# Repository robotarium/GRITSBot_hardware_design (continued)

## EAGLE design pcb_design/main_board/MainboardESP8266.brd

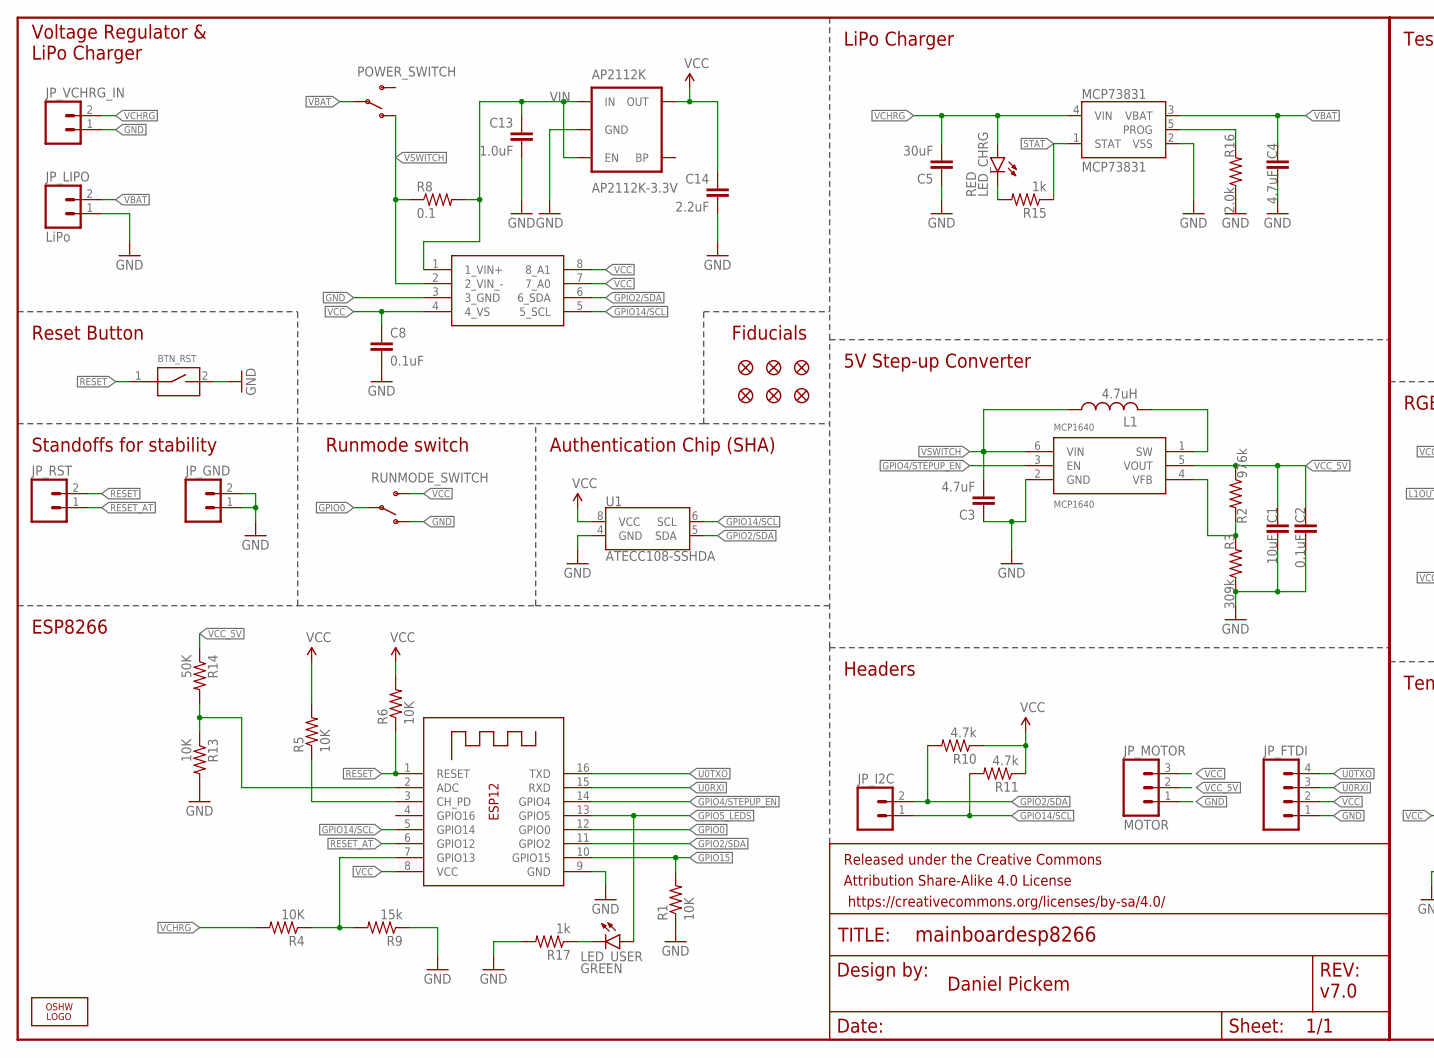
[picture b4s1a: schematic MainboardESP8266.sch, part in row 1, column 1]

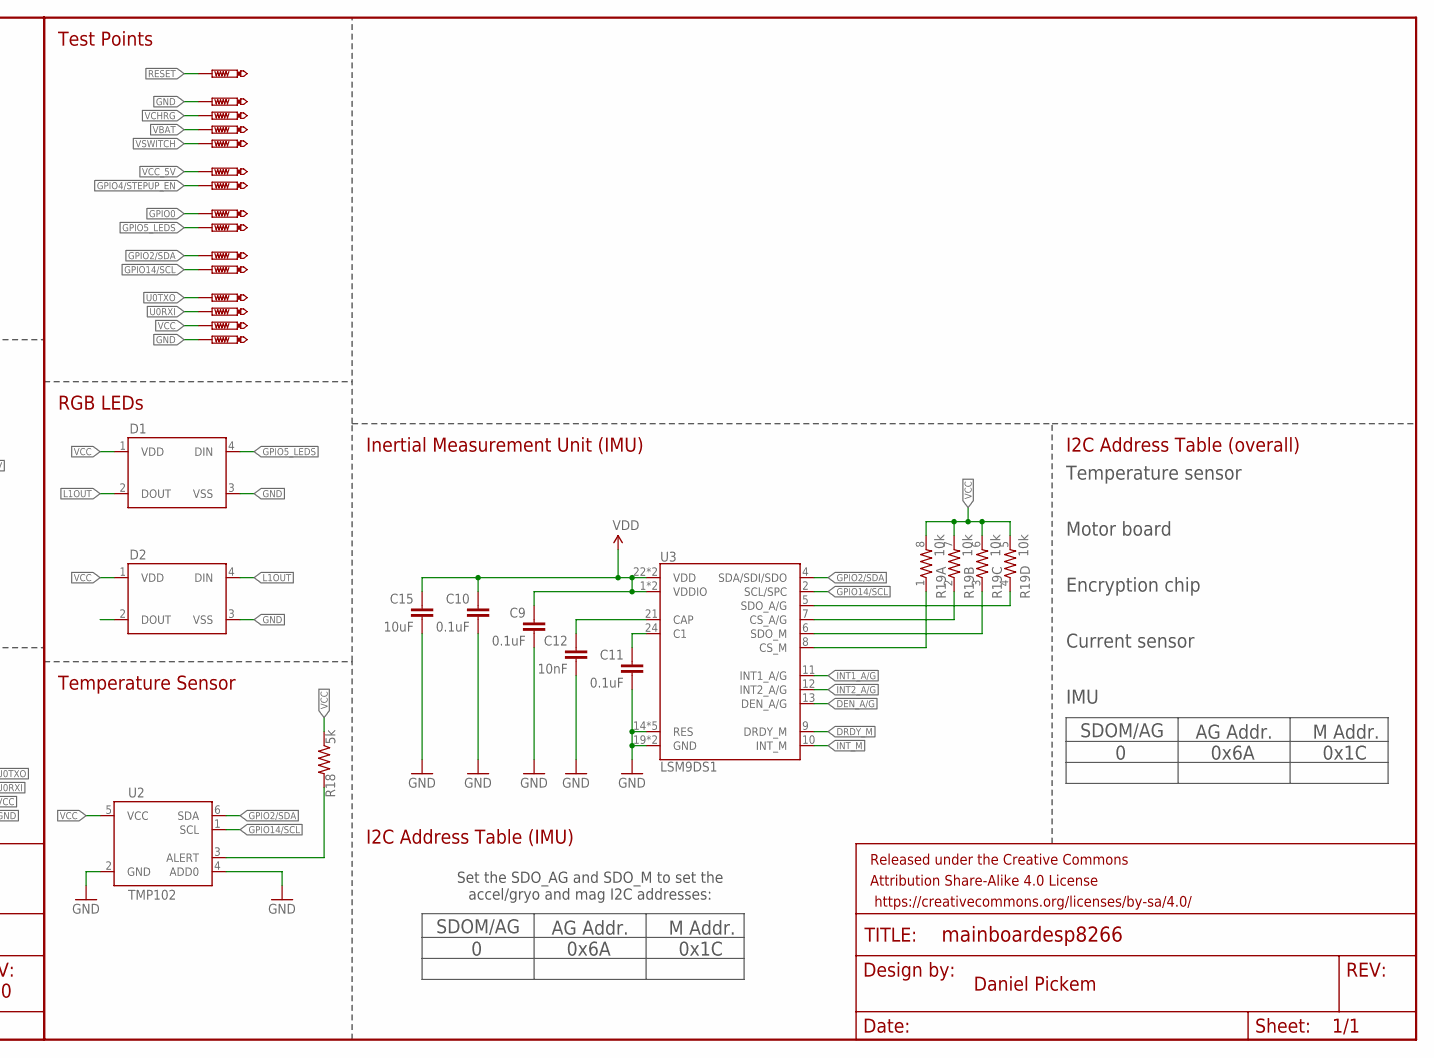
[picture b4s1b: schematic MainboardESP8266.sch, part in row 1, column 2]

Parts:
AP2112K: AP2112K-3.3V; SOT23-5
BTN_RST: BUTTON_TACTILE_SLIM
C1: 10uF; 0603-CAP@1
C2, C8: 0.1uF; 0603-CAP@1
C3, C4: 4.7uF; 0603-CAP@1
C5: 30uF; 1206
C9, C10, C11: 0.1uF; 0603-CAP
C12: 10nF; 0603-CAP
C13: 1.0uF; 0805
C14: 2.2uF; 0603-CAP@1
C15: 10uF; 0603-CAP
D1, D2: WS2812B
ESP8266: ESP-12; ESP-12-07
FRAME1, FRAME2: FRAME-LETTER; CREATIVE_COMMONS
INA219: INA219; SOT-23-8
JP1, JP2, JP3, JP4, JP5, JP6: FIDUCIAL1X2.5; FIDUCIAL-1X2.5
JP_FTDI: M041X04_NO_SILK; 1X04_NO_SILK
JP_GND: M021X02_NO_SILK; 1X02_NO_SILK
JP_I2C: M02PTH; 1X02
JP_LIPO: LiPo; 1X02
JP_MOTOR: MOTOR; 1X03
JP_RST: M021X02_NO_SILK; 1X02_NO_SILK
JP_VCHRG_IN: M021X02_NO_SILK; 1X02_NO_SILK
L1: 4.7uH; INDUCTOR_NR3015
LED_CHRG: RED; LED-0603
LED_USER: GREEN; LED-0603
LOGO1: OSHW_LOGO_FILLX0100-NT; OSHW_FILLX100_NOTEXT
MCP1640: MCP1640; SOT23-6-MCP1640
MCP73831: MCP73831; SOT23-5
POWER_SWITCH: SWITCH-SPDT-SMD-A; SWITCH-SPST-SMD-A
R1, R4, R5, R6, R13: 10K; 0603-RES@1
R2: 976k; 0603-RES@1
R3: 309k; 0603-RES@1
R8: 0.1; 1206
R9: 15k; 0603-RES@1
R10, R11: 4.7k; 0603
R14: 50K; 0603-RES@1
R15, R17: 1k; 0603-RES@1
R16: 2.0k; 0603-RES@1
R18: 5k; 0603-RES@1
R19: 10k; 0603-ARV
RUNMODE_SWITCH: SWITCH-SPDT-SMD-A; SWITCH-SPST-SMD-A
TP1, TP2, TP3, TP4, TP5, TP6, TP7, TP8, TP9, TP10, TP11, TP12, TP13, TP14, TP15: PTR1B1,27; B1,27
U1: ATECC108-SSHDA; SO08
U2: TMP102; SOT563
U3: LSM9DS1; LGA24-8X4

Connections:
ADC: ESP8266.2 (ADC), R13.1, R14.2
C1: C11.1, U3.24 (C1)
CAP: C12.1, U3.21 (CAP)
CHIP_EN1: ESP8266.3 (CH_PD), R5.1
CS_A/G: R19.2 (1), U3.7 (CS_A/G)
CS_M: R19.1, U3.8 (CS_M)
DEN_A/G: U3.13 (DEN_A/G)
DRDY_M: U3.9 (DRDY_M)
GND: AP2112K.2 (GND), BTN_RST.2, C1.2, C2.2, C3.1, C4.2, C5.1, C8.2, C9.2, C10.2, C11.2, C12.2, C13.2, C14.2, C15.2, D1.3 (VSS), D2.3 (VSS), ESP8266.9 (GND), INA219.3 (3_GND), JP_FTDI.1, JP_GND.1, JP_GND.2, JP_LIPO.1, JP_MOTOR.1, JP_VCHRG_IN.1, MCP1640.2 (GND), MCP73831.2 (VSS), R1.1, R3.1, R9.1, R13.2, R16.1, R17.2, RUNMODE_SWITCH.1 (O), TP5.TP, TP8.TP, U1.4 (GND), U2.2 (GND), U2.4 (ADD0), U3.14 (RES), U3.15 (RES), U3.16 (RES), U3.17 (RES), U3.18 (RES), U3.19 (GND), U3.20 (GND)
GPIO0: ESP8266.12 (GPIO0), RUNMODE_SWITCH.2, TP14.TP
GPIO2/SDA: ESP8266.11 (GPIO2), INA219.6 (6_SDA), JP_I2C.2, R10.2, TP6.TP, U1.5 (SDA), U2.6 (SDA), U3.4 (SDA/SDI/SDO)
GPIO4/STEPUP_EN: ESP8266.14 (GPIO4), MCP1640.3 (EN), TP12.TP
GPIO5_LEDS: D1.4 (DIN), ESP8266.13 (GPIO5), LED_USER.A, TP15.TP
GPIO14/SCL: ESP8266.5 (GPIO14), INA219.5 (5_SCL), JP_I2C.1, R11.2, TP7.TP, U1.6 (SCL), U2.1 (SCL), U3.2 (SCL/SPC)
GPIO15: ESP8266.10 (GPIO15), R1.2
INT1_A/G: U3.11 (INT1_A/G)
INT2_A/G: U3.12 (INT2_A/G)
INT_M: U3.10 (INT_M)
L1OUT: D1.2 (DOUT), D2.4 (DIN)
L2OUT: D2.2 (DOUT)
unnamed: LED_CHRG.C, R15.2
unnamed: MCP73831.5 (PROG), R16.2
unnamed: MCP1640.4 (VFB), R2.2, R3.2
unnamed: ESP8266.7 (GPIO13), R4.1, R9.2
unnamed: R18.2, U2.3 (ALERT)
unnamed: L1.P$2 (2), MCP1640.1 (SW)
unnamed: LED_USER.C, R17.1
RESET: BTN_RST.1, ESP8266.1 (RESET), JP_RST.2, R6.1, TP1.TP
RESET_AT: ESP8266.6 (GPIO12), JP_RST.1
SDO_A/G: R19.4 (1), U3.5 (SDO_A/G)
SDO_M: R19.3 (1), U3.6 (SDO_M)
STAT: MCP73831.1 (STAT), R15.1
U0RXI: ESP8266.15 (RXD), JP_FTDI.3, TP3.TP
U0TXO: ESP8266.16 (TXD), JP_FTDI.4, TP2.TP
VBAT: C4.1, JP_LIPO.2, MCP73831.3 (VBAT), POWER_SWITCH.2, TP9.TP
VCC: AP2112K.5 (OUT), C8.1, C9.1, C10.1, C14.1, C15.1, D1.1 (VDD), D2.1 (VDD), ESP8266.8 (VCC), INA219.4 (4_VS), INA219.7 (7_A0), INA219.8 (8_A1), JP_FTDI.2, JP_MOTOR.3, R5.2, R6.2, R10.1, R11.1, R18.1, R19.5 (2), R19.6 (2), R19.7 (2), R19.8 (2), RUNMODE_SWITCH.3 (S), TP4.TP, U1.8 (VCC), U2.5 (VCC), U3.1 (VDDIO), U3.3 (VDDIO), U3.22 (VDD), U3.23 (VDD)
VCC_5V: C1.1, C2.1, JP_MOTOR.2, MCP1640.5 (VOUT), R2.1, R14.1, TP13.TP
VCHRG: C5.2, JP_VCHRG_IN.2, LED_CHRG.A, MCP73831.4 (VIN), R4.2, TP11.TP
VIN: AP2112K.1 (IN), AP2112K.3 (EN), C13.1, INA219.1 (1_VIN+), R8.2
VSWITCH: C3.2, INA219.2 (2_VIN_-), L1.P$1 (1), MCP1640.6 (VIN), POWER_SWITCH.1 (O), R8.1, TP10.TP

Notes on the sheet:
Daniel Pickem
Voltage Regulator & LiPo Charger
ESP8266
Headers
v7.0
5V Step-up Converter
Authentication Chip (SHA)
Standoffs for stability
Runmode switch
Fiducials
Reset Button
LiPo Charger
Test Points
RGB LEDs
Temperature Sensor
Set the SDO_AG and SDO_M to set the accel/gryo and mag I2C addresses:
I2C Address Table (IMU)
Inertial Measurement Unit (IMU)
I2C Address Table (overall)
SDOM/AG
0x1C
AG Addr.
M Addr.
0x6A
IMU
Current sensor
Temperature sensor
Motor board
Encryption chip

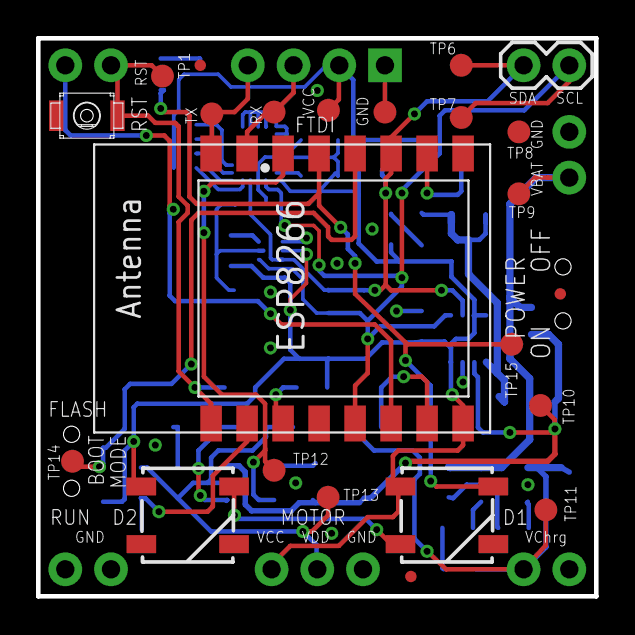
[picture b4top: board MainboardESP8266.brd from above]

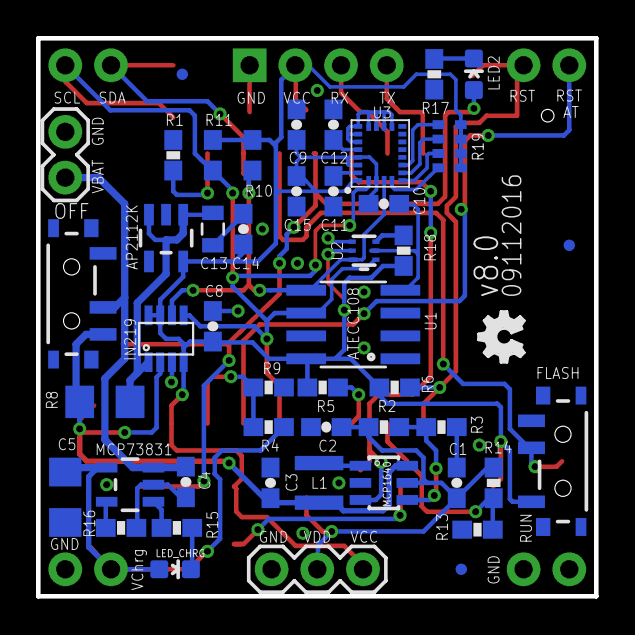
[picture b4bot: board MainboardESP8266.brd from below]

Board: 2 copper layers, 31.0 x 31.0 mm, 77 parts (49 on the bottom side), 34 nets.

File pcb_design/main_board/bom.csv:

Part/Designator,Manufacture Part Number/Seeed SKU,Quantity,Info,DigiKey part #,Ebay Link
AP2112K,AP2112K-3.3TRG1,1,voltage regulator,AP2112K-3.3TRG1DICT-ND,
BTN_RST,PTS820 J15M SMTR LFS,1,reset button,CKN10506CT-ND,
"C1, C15",CC0603MRX5R6BB106,1,10uF,311-1817-1-ND,
"C2, C8, C9, C10, C11",CC0603KRX7R7BB104,2,0.1uF,311-1088-1-ND,
"C3, C4",CL10A475KO8NNNC,2,4.7uF,1276-1784-1-ND,
C5,C3216JB1E336M160AC,1,30uF,445-11710-1-ND,
C12,CC0603JRX7R9BB103,1,10nF,311-1778-1-ND,
C13,CC0603ZRY5V7BB105,1,1.0uF,311-1372-1-ND,
C14,CC0603KRX5R6BB225,1,2.2uF,311-1451-1-ND,
"D1, D2",1528-1104-ND,2,WS2812 RGB LED,1528-1104-ND,
ESP8266,1528-1438-ND,1,Digikey (Adafruit: #2491),1528-1438-ND,
INA219,INA219AIDCNR,1,current monitor chip,296-23770-1-ND,
JP_FTDI,M20-9990446,1,"4 pin, 0.254mm pitch, male header pin",952-2266-ND,
"JP_GND, JP_I2C, JP_RST, JP_VCHRG_IN",M20-9990246,4,"2 pin, 0.254mm pitch male header pin",952-2262-ND,
JP_MOTOR,PPPC031LFBN-RC ,1,"3 pin, 0.254mm pitch female header pin",S7036-ND,
JP_LIPO,Losi Micro Walkera 2-Pin Connector plug,1,,,e.g. http://www.ebay.com/itm/Losi-Micro-Walkera-2-Pin-Connector-p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
L1,NR3015T4R7M,1,4.7uH,587-1649-1-ND,
LED_CHRG,5988020107F,1,red,350-2030-1-ND,
LED_USER,5988060107F,1,green,350-2034-1-ND,
MCP1640,MCP1640BT-I/CHY,1,Boost converter,MCP1640BT-I/CHYCT-ND,
MCP73831,MCP73831T-2ACI/OT,1,LiPo charging chip,MCP73831T-2ACI/OTCT-ND,
"POWER_SWITCH, RUNMODE_SWITCH",PCM12SMTR,2,switches,401-2016-1-ND,
"R1, R4, R5, R6, R13",RC0603FR-0710KL,6,10k,311-10.0KHRCT-ND,
R2,RC0603FR-07976KL,1,976k,311-976KHRCT-ND,
R3,RC0603FR-07309KL,1,309k,311-309KHRCT-ND,
R8,ERJ-8BWFR100V,1,0.1,P.10AUCT-ND,
R9,RC0603FR-0715KL ,2,15k,311-15.0KHRCT-ND,
"R10, R11",RC0603FR-074K7L ,2,4.7k,311-4.70KHRCT-ND ,
R16,RC0603FR-072KL,1,2.0k,311-2.00KHRCT-ND,
"R15, R17",RC0603FR-071KL,2,1.0k,311-1.00KHRCT-ND,
R18,RC0603FR-074K99L ,1,4.99k,311-4.99KHRCT-ND,
R14,RC0603FR-0749K9L,1,50k,311-49.9KHRCT-ND,
R19,742C083103JP ,1,10k resistor array,742C083103JPCT-ND,
U1,ATECC108A-SSHCZ-B,1,encryption chip,ATECC108A-SSHCZ-B-ND,
U2,TMP102AIDRLR ,1,TMP102 temperature sensor,296-26834-1-ND ,
U3,LSM9DS1TR,1,LSM9DS1 IMU,497-14946-1-ND ,

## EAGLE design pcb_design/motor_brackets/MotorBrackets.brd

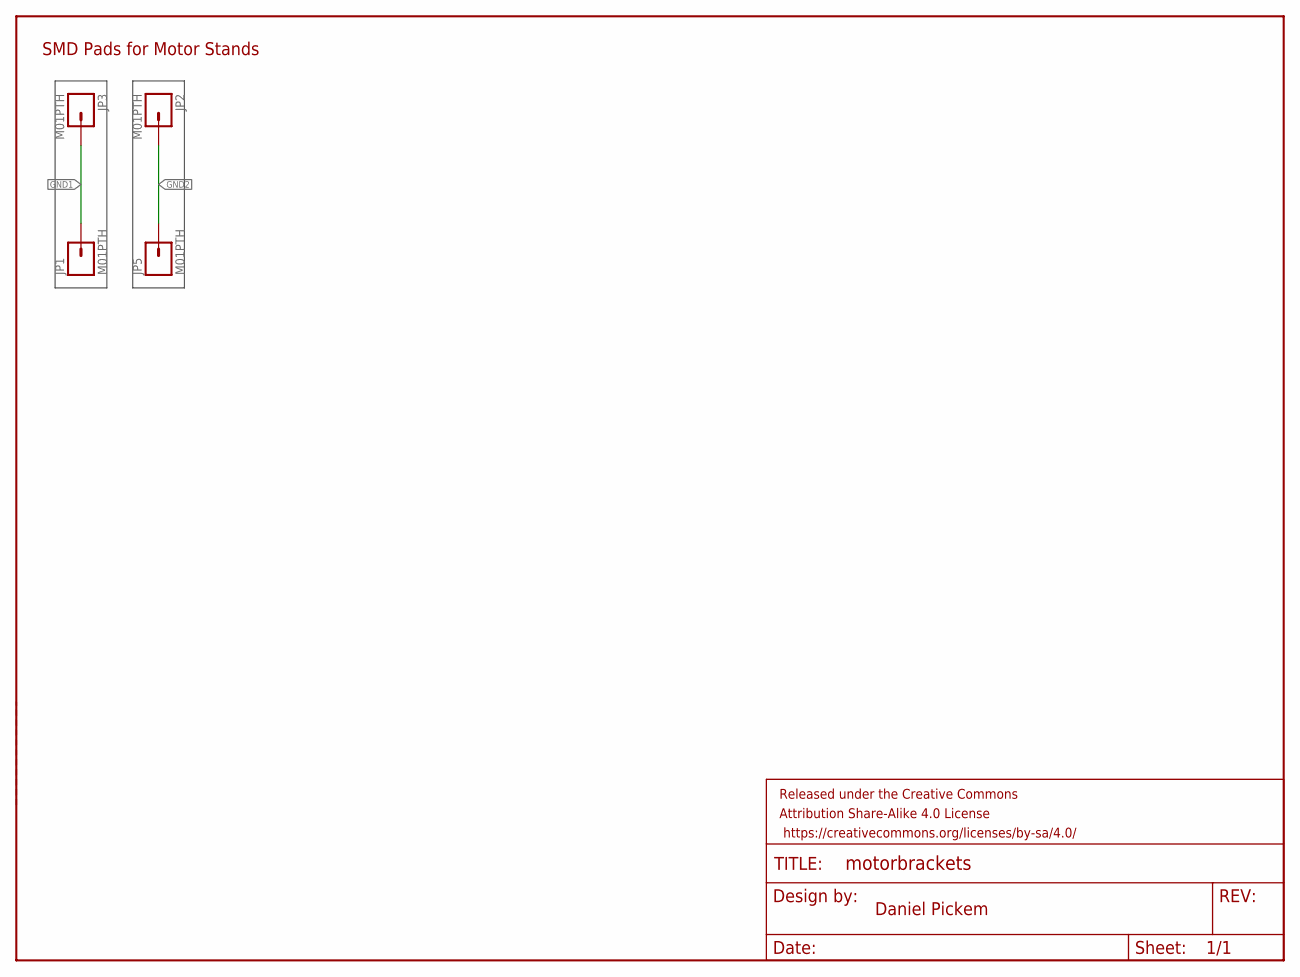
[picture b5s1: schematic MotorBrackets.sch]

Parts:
FRAME1: FRAME-LETTER; CREATIVE_COMMONS
JP1, JP2, JP3, JP5: M01PTH; 1X01

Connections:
GND1: JP1.1, JP3.1
GND2: JP2.1, JP5.1

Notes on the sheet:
Daniel Pickem
SMD Pads for Motor Stands

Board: 2 copper layers, 5 parts (0 on the bottom side), 2 nets, no tracks yet.

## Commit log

2016-09-13 Added schematic and PCB design for the GRITSBot main board
2016-09-13 Added schematic and PCB design for the GRITSBot motor board
2016-09-13 Added motor brackets for the GRITSBot's motor board
    These motor brackets are made out of PCB material like the main
    and motor board of the robot. Each bracket is glued to the motor
    board and functions as caster pins so that the robot is statically
    stable. Note that these motor brackets can be replaced with the
    3D printed part that also functions as charging coil mount (see
    folder '3d_model' in this repository.
2016-09-13 Added 3D model of the robot
2016-09-13 Added prototype of GRITSBot shell
2016-09-13 Added charging coil mount
2016-09-13 Added 3D model of robot including its shell
2016-09-13 Added bill of materials for GRITSBot
    The bill of materials (BoM) includes the BoM for the main board,
    the motor board, as well as additional components needed to
    assemble the robot.
2016-09-13 Added license information
2016-09-15 Added images of the latest main and motor board prototypes
2016-09-15 Updated README file
2016-10-19 Updated the GRITSBot's motor board
    1. Added a reset pin so that the main board can reset
    the motor board.
    2. Fixed the polarity of the current sensors.
    3. Added test pins on the top layer.
    4. Added castellated edges to mount motors mechanically
    more stable.
2016-10-25 Moved test points to allow for pogo pins on test board
2016-10-25 Removed reverse polarity protection on charge input
2016-10-25 Added IMU and temperature sensor to main board
2016-11-02 Fixed RGB LED setup on main board.
    The RGB LEDs were connected to GPIO16, which on some versions
    of the ESP8266 is connected to the RESET pin and can't be used
    as general purpose pin after all. The RGB LEDs are now connected
    to GPIO5 - the same pin as the status LED. Both types of LEDs can
    be used together on the same pin.
2016-11-04 Moved test pads to account for pogo pin holes on tester boards
2016-11-09 Merged Main Board Test pin location changes into master
2016-11-09 Added test pin for GPIO5
2016-11-09 Changed LED color value on motor board
2016-11-09 Added BoM for main and motor board
2016-11-14 Minor silk screen changes to mMotor board
2016-11-14 Minor comment change on motor board schematic
2016-12-05 TestBoard Designs
2016-12-05 Added TODO comments on test board designs
